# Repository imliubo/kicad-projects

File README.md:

# kicad-projects

My opensource kicad projects.

1. [D1-MIPI-LCD转接板](./01-D1-MIPI-LCD/README.md)
2. [LED-Matrix-12x16](./02-CH32V203-LED-Matrix-12x16/)

## 重要‼️

本人不是硬件工程师, 不能完全保证本仓库开源的设计是100%没问题或者可以直接批量生产的, 如果由设计缺陷造成的任何损失, 本人不承担责任.
也欢迎大家提PR~

## LICENSE-MIT

本仓库的项目没做特殊说明都是MIT协议, 大家可以随意复制修改~
如果觉得有帮助, 可以Link一下本仓库(感谢).

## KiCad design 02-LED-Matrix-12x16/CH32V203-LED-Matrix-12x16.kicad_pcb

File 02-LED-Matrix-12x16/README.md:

# LED-Matrix-12x16

## 简要说明

* KiCad版本是9.0.2
* 主控MCU是WCH的CH32V203C8U6
* LED的封装是0402, 一共192颗
* BOOT拉高进入USB下载模式, 可以不用WCH-Link
* 要调试可以用调试接口, 1.27mm间距

## 代码

模拟蜡烛效果目前效果还很差, 能搞好了再说吧 ==.

## wchisp

```bash
wchisp flash CH32V203-LED-Matrix-12x16.hex
```

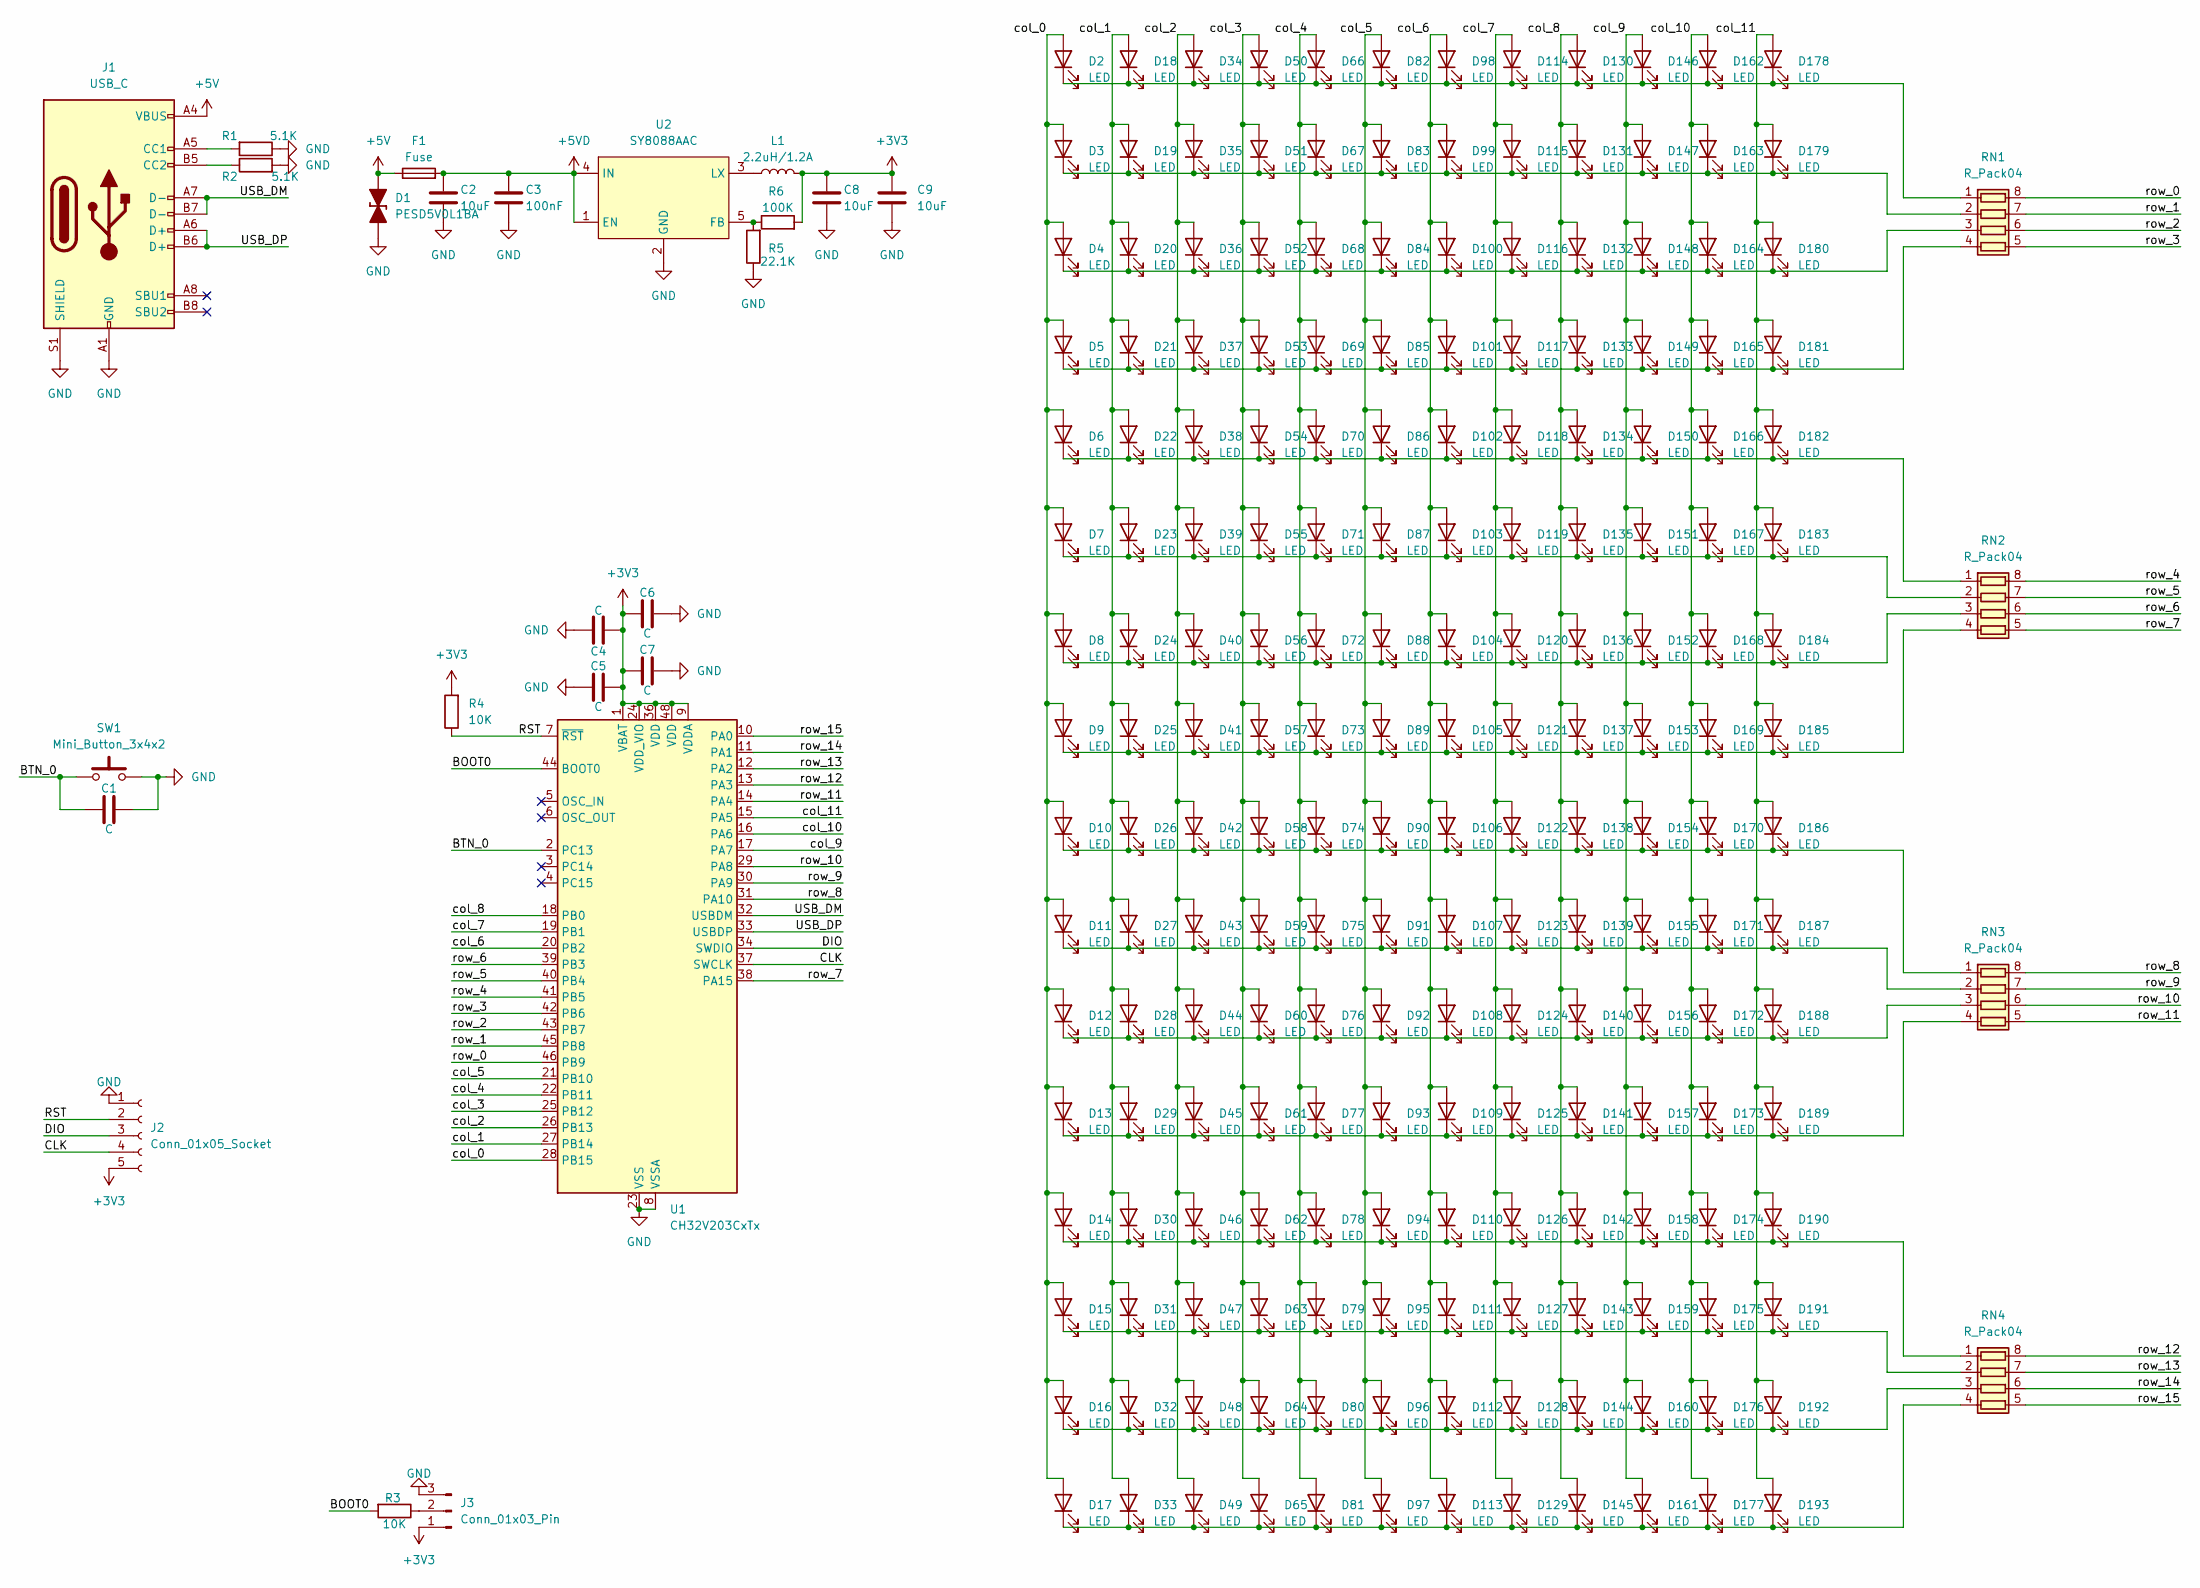
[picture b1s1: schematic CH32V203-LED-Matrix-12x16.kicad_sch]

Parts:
C1, C4, C5, C6, C7: C; C_0402_1005Metric
C2, C8, C9: 10uF; C_0402_1005Metric
C3: 100nF; C_0402_1005Metric
D1: PESD5V0L1BA; D_SOD-323
D2, D3, D4, D5, D6, D7, D8, D9, D10, D11, D12, D13, D14, D15, D16, D17, D18, D19, D20, D21, D22, D23, D24, D25, D26, D27, D28, D29, D30, D31, D32, D33, D34, D35, D36, D37, D38, D39, D40, D41, D42, D43, D44, D45, D46, D47, D48, D49, D50, D51, D52, D53, D54, D55, D56, D57, D58, D59, D60, D61, D62, D63, D64, D65, D66, D67, D68, D69, D70, D71, D72, D73, D74, D75, D76, D77, D78, D79, D80, D81, D82, D83, D84, D85, D86, D87, D88, D89, D90, D91, D92, D93, D94, D95, D96, D97, D98, D99, D100, D101, D102, D103, D104, D105, D106, D107, D108, D109, D110, D111, D112, D113, D114, D115, D116, D117, D118, D119, D120, D121, D122, D123, D124, D125, D126, D127, D128, D129, D130, D131, D132, D133, D134, D135, D136, D137, D138, D139, D140, D141, D142, D143, D144, D145, D146, D147, D148, D149, D150, D151, D152, D153, D154, D155, D156, D157, D158, D159, D160, D161, D162, D163, D164, D165, D166, D167, D168, D169, D170, D171, D172, D173, D174, D175, D176, D177, D178, D179, D180, D181, D182, D183, D184, D185, D186, D187, D188, D189, D190, D191, D192, D193: LED; LED_0402_1005Metric_Pad0.77x0.64mm_HandSolder
F1: Fuse; Fuse_1206_3216Metric
J1: USB_C
J2: Conn_01x05_Socket; PinHeader_1x05_P1.27mm_Vertical
J3: Conn_01x03_Pin; PinHeader_1x03_P1.27mm_Vertical
L1: 2.2uH/1.2A; L_Changjiang_FNR4020S
R1, R2: 5.1K; R_0402_1005Metric_Pad0.72x0.64mm_HandSolder
R3, R4: 10K; R_0402_1005Metric_Pad0.72x0.64mm_HandSolder
R5: 22.1K; R_0402_1005Metric_Pad0.72x0.64mm_HandSolder
R6: 100K; R_0402_1005Metric_Pad0.72x0.64mm_HandSolder
RN1, RN2, RN3, RN4: R_Pack04; R_Array_Convex_4x0402
SW1: Mini_Button_3x4x2; Button_2Pin_3x4x2
U1: CH32V203CxTx; QFN-48-1EP_7x7mm_P0.5mm_EP5.3x5.3mm
U2: SY8088AAC; SOT-23-5

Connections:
+3V3: C4.2, C5.1, C6.2, C7.2, C8.1, C9.1, J2.5, J3.1, L1.2, R4.2, R6.2, U1.1 (VBAT), U1.9 (VDDA), U1.24 (VDD_VIO), U1.36 (VDD), U1.48 (VDD)
+5V: D1.2 (A), F1.1, J1.A4 (VBUS), J1.A9 (VBUS), J1.B4 (VBUS), J1.B9 (VBUS)
+5VD: C2.1, C3.1, F1.2, U2.1 (EN), U2.4 (IN)
/BOOT0: R3.2, U1.44 (BOOT0)
/BTN_0: C1.2, SW1.A (1), U1.2 (PC13)
/CLK: J2.4, U1.37 (SWCLK)
/DIO: J2.3, U1.34 (SWDIO)
/RST: J2.2, R4.1, U1.7 (~RST)
/USB_DM: J1.A7 (D-), J1.B7 (D-), U1.32 (USBDM)
/USB_DP: J1.A6 (D+), J1.B6 (D+), U1.33 (USBDP)
/col_0: D2.2 (A), D3.2 (A), D4.2 (A), D5.2 (A), D6.2 (A), D7.2 (A), D8.2 (A), D9.2 (A), D10.2 (A), D11.2 (A), D12.2 (A), D13.2 (A), D14.2 (A), D15.2 (A), D16.2 (A), D17.2 (A), U1.28 (PB15)
/col_1: D18.2 (A), D19.2 (A), D20.2 (A), D21.2 (A), D22.2 (A), D23.2 (A), D24.2 (A), D25.2 (A), D26.2 (A), D27.2 (A), D28.2 (A), D29.2 (A), D30.2 (A), D31.2 (A), D32.2 (A), D33.2 (A), U1.27 (PB14)
/col_2: D34.2 (A), D35.2 (A), D36.2 (A), D37.2 (A), D38.2 (A), D39.2 (A), D40.2 (A), D41.2 (A), D42.2 (A), D43.2 (A), D44.2 (A), D45.2 (A), D46.2 (A), D47.2 (A), D48.2 (A), D49.2 (A), U1.26 (PB13)
/col_3: D50.2 (A), D51.2 (A), D52.2 (A), D53.2 (A), D54.2 (A), D55.2 (A), D56.2 (A), D57.2 (A), D58.2 (A), D59.2 (A), D60.2 (A), D61.2 (A), D62.2 (A), D63.2 (A), D64.2 (A), D65.2 (A), U1.25 (PB12)
/col_4: D66.2 (A), D67.2 (A), D68.2 (A), D69.2 (A), D70.2 (A), D71.2 (A), D72.2 (A), D73.2 (A), D74.2 (A), D75.2 (A), D76.2 (A), D77.2 (A), D78.2 (A), D79.2 (A), D80.2 (A), D81.2 (A), U1.22 (PB11)
/col_5: D82.2 (A), D83.2 (A), D84.2 (A), D85.2 (A), D86.2 (A), D87.2 (A), D88.2 (A), D89.2 (A), D90.2 (A), D91.2 (A), D92.2 (A), D93.2 (A), D94.2 (A), D95.2 (A), D96.2 (A), D97.2 (A), U1.21 (PB10)
/col_6: D98.2 (A), D99.2 (A), D100.2 (A), D101.2 (A), D102.2 (A), D103.2 (A), D104.2 (A), D105.2 (A), D106.2 (A), D107.2 (A), D108.2 (A), D109.2 (A), D110.2 (A), D111.2 (A), D112.2 (A), D113.2 (A), U1.20 (PB2)
/col_7: D114.2 (A), D115.2 (A), D116.2 (A), D117.2 (A), D118.2 (A), D119.2 (A), D120.2 (A), D121.2 (A), D122.2 (A), D123.2 (A), D124.2 (A), D125.2 (A), D126.2 (A), D127.2 (A), D128.2 (A), D129.2 (A), U1.19 (PB1)
/col_8: D130.2 (A), D131.2 (A), D132.2 (A), D133.2 (A), D134.2 (A), D135.2 (A), D136.2 (A), D137.2 (A), D138.2 (A), D139.2 (A), D140.2 (A), D141.2 (A), D142.2 (A), D143.2 (A), D144.2 (A), D145.2 (A), U1.18 (PB0)
/col_9: D146.2 (A), D147.2 (A), D148.2 (A), D149.2 (A), D150.2 (A), D151.2 (A), D152.2 (A), D153.2 (A), D154.2 (A), D155.2 (A), D156.2 (A), D157.2 (A), D158.2 (A), D159.2 (A), D160.2 (A), D161.2 (A), U1.17 (PA7)
/col_10: D162.2 (A), D163.2 (A), D164.2 (A), D165.2 (A), D166.2 (A), D167.2 (A), D168.2 (A), D169.2 (A), D170.2 (A), D171.2 (A), D172.2 (A), D173.2 (A), D174.2 (A), D175.2 (A), D176.2 (A), D177.2 (A), U1.16 (PA6)
/col_11: D178.2 (A), D179.2 (A), D180.2 (A), D181.2 (A), D182.2 (A), D183.2 (A), D184.2 (A), D185.2 (A), D186.2 (A), D187.2 (A), D188.2 (A), D189.2 (A), D190.2 (A), D191.2 (A), D192.2 (A), D193.2 (A), U1.15 (PA5)
/row_0: RN1.8 (R1.2), U1.46 (PB9)
/row_1: RN1.7 (R2.2), U1.45 (PB8)
/row_2: RN1.6 (R3.2), U1.43 (PB7)
/row_3: RN1.5 (R4.2), U1.42 (PB6)
/row_4: RN2.8 (R1.2), U1.41 (PB5)
/row_5: RN2.7 (R2.2), U1.40 (PB4)
/row_6: RN2.6 (R3.2), U1.39 (PB3)
/row_7: RN2.5 (R4.2), U1.38 (PA15)
/row_8: RN3.8 (R1.2), U1.31 (PA10)
/row_9: RN3.7 (R2.2), U1.30 (PA9)
/row_10: RN3.6 (R3.2), U1.29 (PA8)
/row_11: RN3.5 (R4.2), U1.14 (PA4)
/row_12: RN4.8 (R1.2), U1.13 (PA3)
/row_13: RN4.7 (R2.2), U1.12 (PA2)
/row_14: RN4.6 (R3.2), U1.11 (PA1)
/row_15: RN4.5 (R4.2), U1.10 (PA0)
GND: C1.1, C2.2, C3.2, C4.1, C5.2, C6.1, C7.1, C8.2, C9.2, D1.1 (K), J1.A1 (GND), J1.A12 (GND), J1.B1 (GND), J1.B12 (GND), J1.S1 (SHIELD), J2.1, J3.3, R1.1, R2.2, R5.1, SW1.K (2), U1.8 (VSSA), U1.23 (VSS), U1.35 (VSS), U1.47 (VSS), U2.2 (GND)
unnamed: D10.1 (K), D26.1 (K), D42.1 (K), D58.1 (K), D74.1 (K), D90.1 (K), D106.1 (K), D122.1 (K), D138.1 (K), D154.1 (K), D170.1 (K), D186.1 (K), RN3.1 (R1.1)
unnamed: D4.1 (K), D20.1 (K), D36.1 (K), D52.1 (K), D68.1 (K), D84.1 (K), D100.1 (K), D116.1 (K), D132.1 (K), D148.1 (K), D164.1 (K), D180.1 (K), RN1.3 (R3.1)
unnamed: D5.1 (K), D21.1 (K), D37.1 (K), D53.1 (K), D69.1 (K), D85.1 (K), D101.1 (K), D117.1 (K), D133.1 (K), D149.1 (K), D165.1 (K), D181.1 (K), RN1.4 (R4.1)
unnamed: D6.1 (K), D22.1 (K), D38.1 (K), D54.1 (K), D70.1 (K), D86.1 (K), D102.1 (K), D118.1 (K), D134.1 (K), D150.1 (K), D166.1 (K), D182.1 (K), RN2.1 (R1.1)
unnamed: D7.1 (K), D23.1 (K), D39.1 (K), D55.1 (K), D71.1 (K), D87.1 (K), D103.1 (K), D119.1 (K), D135.1 (K), D151.1 (K), D167.1 (K), D183.1 (K), RN2.2 (R2.1)
unnamed: D8.1 (K), D24.1 (K), D40.1 (K), D56.1 (K), D72.1 (K), D88.1 (K), D104.1 (K), D120.1 (K), D136.1 (K), D152.1 (K), D168.1 (K), D184.1 (K), RN2.3 (R3.1)
unnamed: D9.1 (K), D25.1 (K), D41.1 (K), D57.1 (K), D73.1 (K), D89.1 (K), D105.1 (K), D121.1 (K), D137.1 (K), D153.1 (K), D169.1 (K), D185.1 (K), RN2.4 (R4.1)
unnamed: D11.1 (K), D27.1 (K), D43.1 (K), D59.1 (K), D75.1 (K), D91.1 (K), D107.1 (K), D123.1 (K), D139.1 (K), D155.1 (K), D171.1 (K), D187.1 (K), RN3.2 (R2.1)
unnamed: D12.1 (K), D28.1 (K), D44.1 (K), D60.1 (K), D76.1 (K), D92.1 (K), D108.1 (K), D124.1 (K), D140.1 (K), D156.1 (K), D172.1 (K), D188.1 (K), RN3.3 (R3.1)
unnamed: D13.1 (K), D29.1 (K), D45.1 (K), D61.1 (K), D77.1 (K), D93.1 (K), D109.1 (K), D125.1 (K), D141.1 (K), D157.1 (K), D173.1 (K), D189.1 (K), RN3.4 (R4.1)
unnamed: D14.1 (K), D30.1 (K), D46.1 (K), D62.1 (K), D78.1 (K), D94.1 (K), D110.1 (K), D126.1 (K), D142.1 (K), D158.1 (K), D174.1 (K), D190.1 (K), RN4.1 (R1.1)
unnamed: D15.1 (K), D31.1 (K), D47.1 (K), D63.1 (K), D79.1 (K), D95.1 (K), D111.1 (K), D127.1 (K), D143.1 (K), D159.1 (K), D175.1 (K), D191.1 (K), RN4.2 (R2.1)
unnamed: D16.1 (K), D32.1 (K), D48.1 (K), D64.1 (K), D80.1 (K), D96.1 (K), D112.1 (K), D128.1 (K), D144.1 (K), D160.1 (K), D176.1 (K), D192.1 (K), RN4.3 (R3.1)
unnamed: D17.1 (K), D33.1 (K), D49.1 (K), D65.1 (K), D81.1 (K), D97.1 (K), D113.1 (K), D129.1 (K), D145.1 (K), D161.1 (K), D177.1 (K), D193.1 (K), RN4.4 (R4.1)
unnamed: D2.1 (K), D18.1 (K), D34.1 (K), D50.1 (K), D66.1 (K), D82.1 (K), D98.1 (K), D114.1 (K), D130.1 (K), D146.1 (K), D162.1 (K), D178.1 (K), RN1.1 (R1.1)
unnamed: D3.1 (K), D19.1 (K), D35.1 (K), D51.1 (K), D67.1 (K), D83.1 (K), D99.1 (K), D115.1 (K), D131.1 (K), D147.1 (K), D163.1 (K), D179.1 (K), RN1.2 (R2.1)
unnamed: J1.A5 (CC1), R1.2
unnamed: J1.B5 (CC2), R2.1
unnamed: J3.2, R3.1
unnamed: R5.2, R6.1, U2.5 (FB)
unnamed: L1.1, U2.3 (LX)

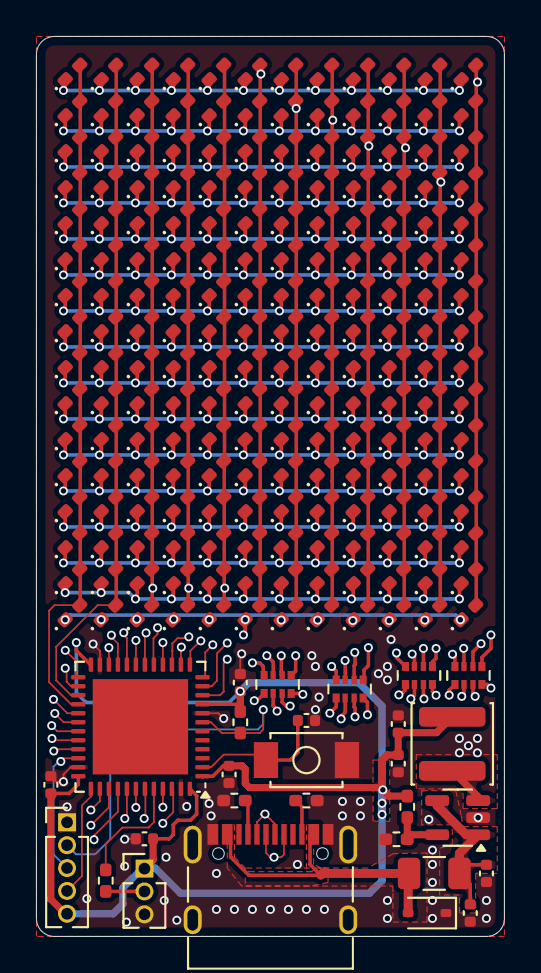
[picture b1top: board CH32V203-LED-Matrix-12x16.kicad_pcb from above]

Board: 4 copper layers, 26.0 x 50.0 mm, 220 parts (0 on the bottom side), 60 nets.

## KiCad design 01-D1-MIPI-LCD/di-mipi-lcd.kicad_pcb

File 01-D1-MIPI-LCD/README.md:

## 哪吒D1 MIPI LCD 转 JD9852 1 Lane 显示屏

[调试帖子-全志在线论坛](https://bbs.aw-ol.com/topic/405/%E7%AC%AC%E4%B8%80%E6%AC%A1%E8%B0%83mipi%E6%8E%A5%E5%8F%A3%E7%9A%84%E6%98%BE%E7%A4%BA%E5%B1%8F-%E9%83%BD%E6%98%AF%E4%BB%80%E4%B9%88%E5%A5%97%E8%B7%AF/7?_=1631200546654)

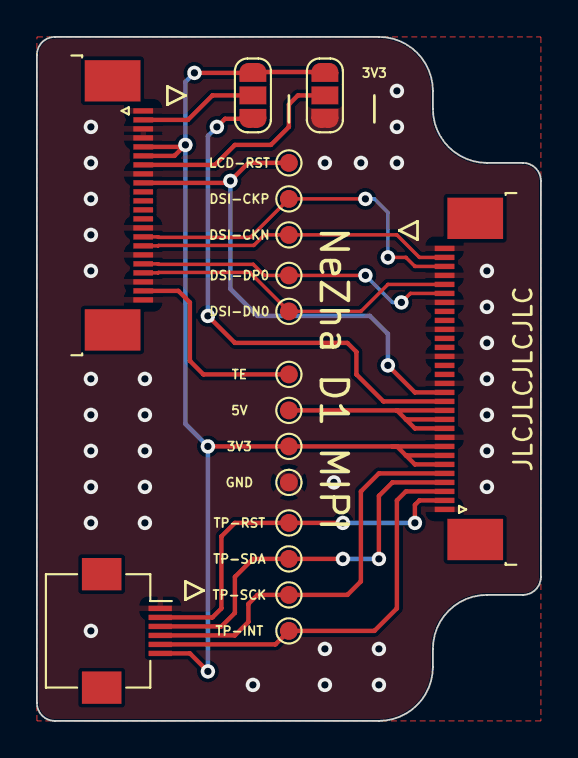
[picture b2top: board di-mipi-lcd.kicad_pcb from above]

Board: 2 copper layers, 28.0 x 38.0 mm, 18 parts (0 on the bottom side), 16 nets.

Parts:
J1: Conn_01x22; TE_2-1734839-2_1x22-1MP_P0.5mm_Horizontal
J2: Conn_01x30; TE_3-1734839-0_1x30-1MP_P0.5mm_Horizontal
J3: Conn_01x06; Hirose_FH12-6S-0.5SH_1x06-1MP_P0.50mm_Horizontal
JP1, JP2: SolderJumper_3_Open; SolderJumper-3_P1.3mm_Open_RoundedPad1.0x1.5mm_NumberLabels
TP1, TP2, TP3, TP4, TP5, TP6, TP7, TP8, TP9, TP10, TP11, TP12, TP13: TestPoint; TestPoint_Pad_D1.0mm

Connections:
+3V3: J1.5, J1.6, J2.6, J2.7, J2.8, J3.6, JP1.3 (B), JP2.3 (B), TP10.1
+5V: J2.10, J2.11, J2.12, TP9.1
/BL-PWM: J2.13, JP1.1 (A)
/DSI-CKN: J1.16, J2.29, TP12.1
/DSI-CKP: J1.15, J2.28, TP11.1
/DSI-DN0: J1.19, J2.26, TP2.1
/DSI-DP0: J1.18, J2.25, TP1.1
/DSI-RST: J1.9, J2.14, TP8.1
/TE: J1.21, TP3.1
/TP-INT: J2.3, J3.5, TP7.1
/TP-RST: J2.2, J3.2, TP4.1
/TP-SCK: J2.5, J3.4, TP6.1
/TP-SDA: J2.4, J3.3, TP5.1
GND: J1.1, J1.3, J1.4, J1.8, J1.14, J1.17, J1.20, J1.22, J2.1, J2.9, J2.15, J2.18, J2.21, J2.24, J2.27, J2.30, J3.1, JP2.1 (A), TP13.1
unnamed: J1.2, JP1.2 (C)
unnamed: J1.7, JP2.2 (C)

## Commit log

2021-09-09 Add D1-MIPI-LCD adapter board project
2025-07-13 增加LED-Matrix项目, 完善README
